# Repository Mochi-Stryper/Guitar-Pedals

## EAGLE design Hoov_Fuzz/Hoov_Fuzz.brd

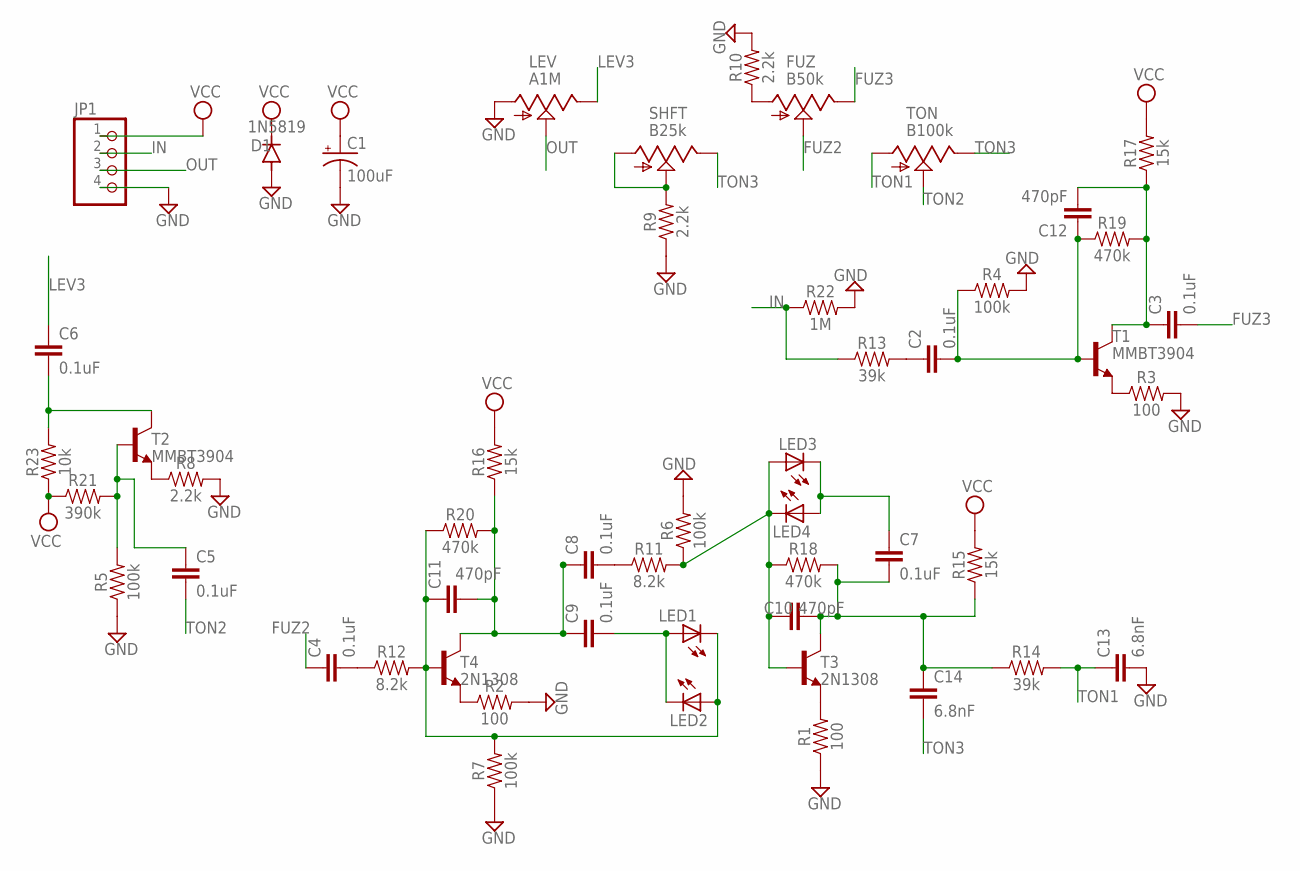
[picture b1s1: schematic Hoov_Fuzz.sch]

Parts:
C1: 100uF; PAN_B_SMD+THRU
C2, C3, C4, C5, C6, C7, C8, C9: 0.1uF; 0603
C10, C11, C12: 470pF; 0603
C13, C14: 6.8nF; 0603
D1: 1N5819; SOD123
FUZ: B50k; 9MM_SNAP-IN_POT
JP1: PINHD-1X4; 1X04
LED1, LED2, LED3, LED4: LED_E; LED_1206
LEV: A1M; 9MM_SNAP-IN_POT
R1, R2, R3: 100; 0603
R4, R5, R6, R7: 100k; 0603
R8, R9, R10: 2.2k; 0603
R11, R12: 8.2k; 0603
R13, R14: 39k; 0603
R15, R16, R17: 15k; 0603
R18, R19, R20: 470k; 0603
R21: 390k; 0603
R22: 1M; 0603
R23: 10k; 0603
SHFT: B25k; 9MM_SNAP-IN_POT
T1, T2: MMBT3904; SOT23-BEC
T3, T4: 2N1308; TO5
TON: B100k; 9MM_SNAP-IN_POT

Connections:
FUZ2: C4.1, FUZ.2 (S)
FUZ3: C3.2, FUZ.3 (E)
GND: C1.-, C1.-- (-), C13.2, D1.A, JP1.4, LEV.1 (A), R1.1, R2.2, R3.2, R4.2, R5.1, R6.2, R7.1, R8.2, R9.1, R10.2, R22.2
IN: JP1.2, R13.1, R22.1
LEV3: C6.1, LEV.3 (E)
unnamed: R9.2, SHFT.1 (A), SHFT.2 (S)
unnamed: C2.1, R13.2
unnamed: C2.2, C12.1, R4.1, R19.1, T1.B
unnamed: FUZ.1 (A), R10.1
unnamed: C3.1, C12.2, R17.1, R19.2, T1.C
unnamed: R3.1, T1.E
unnamed: C4.2, R12.1
unnamed: R2.1, T4.1 (E)
unnamed: C9.2, LED1.A, LED2.C
unnamed: C8.1, C9.1, C11.2, R16.1, R20.2, T4.3 (C)
unnamed: C11.1, LED1.C, LED2.A, R7.2, R12.2, R20.1, T4.2 (B)
unnamed: C8.2, R11.1
unnamed: C10.1, LED3.A, LED4.C, R6.1, R11.2, R18.1, T3.2 (B)
unnamed: C7.2, C10.2, C14.1, R14.1, R15.1, R18.2, T3.3 (C)
unnamed: R1.2, T3.1 (E)
unnamed: C7.1, LED3.C, LED4.A
unnamed: C5.1, R5.2, R21.2, T2.B
unnamed: C6.2, R23.2, T2.C
unnamed: R8.1, T2.E
OUT: JP1.3, LEV.2 (S)
TON1: C13.1, R14.2, TON.1 (A)
TON2: C5.2, TON.2 (S)
TON3: C14.2, SHFT.3 (E), TON.3 (E)
VCC: C1.+, C1.++ (+), D1.C, JP1.1, R15.2, R16.2, R17.2, R21.1, R23.1

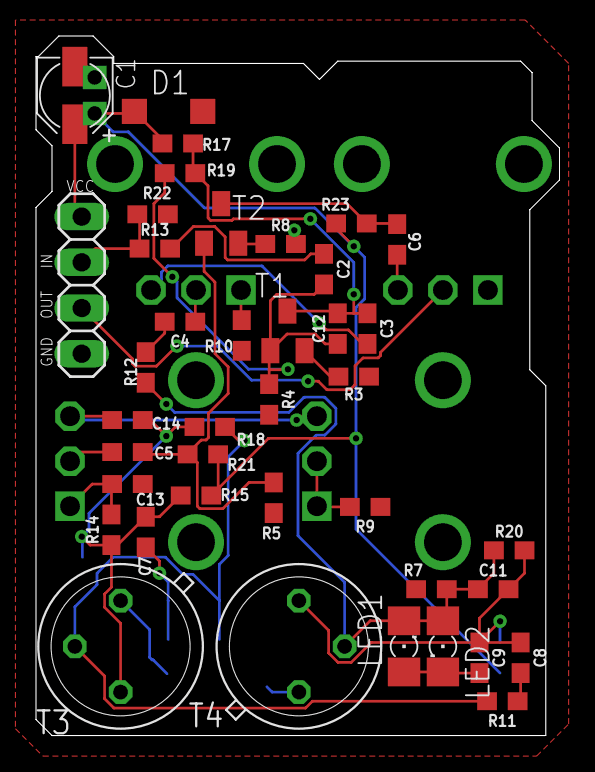
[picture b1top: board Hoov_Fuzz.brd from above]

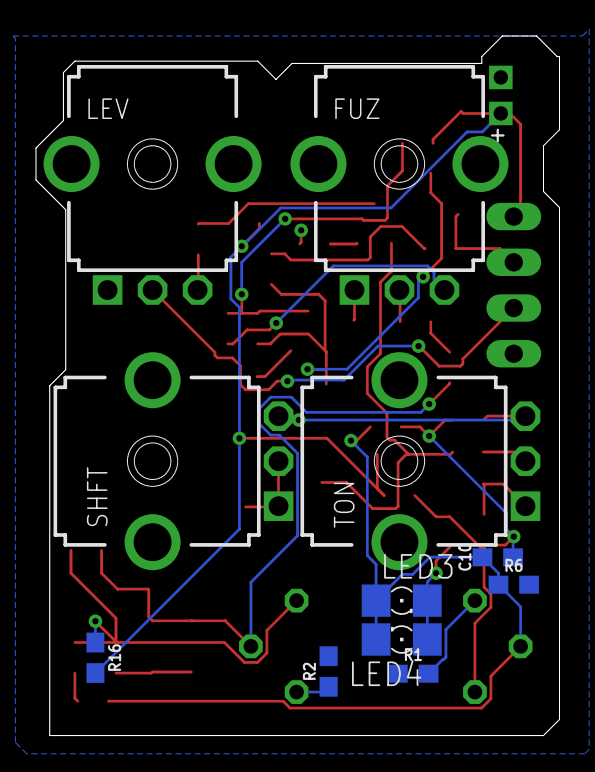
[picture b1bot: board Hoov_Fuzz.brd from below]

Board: 2 copper layers, 29.1 x 38.9 mm, 51 parts (11 on the bottom side), 29 nets.

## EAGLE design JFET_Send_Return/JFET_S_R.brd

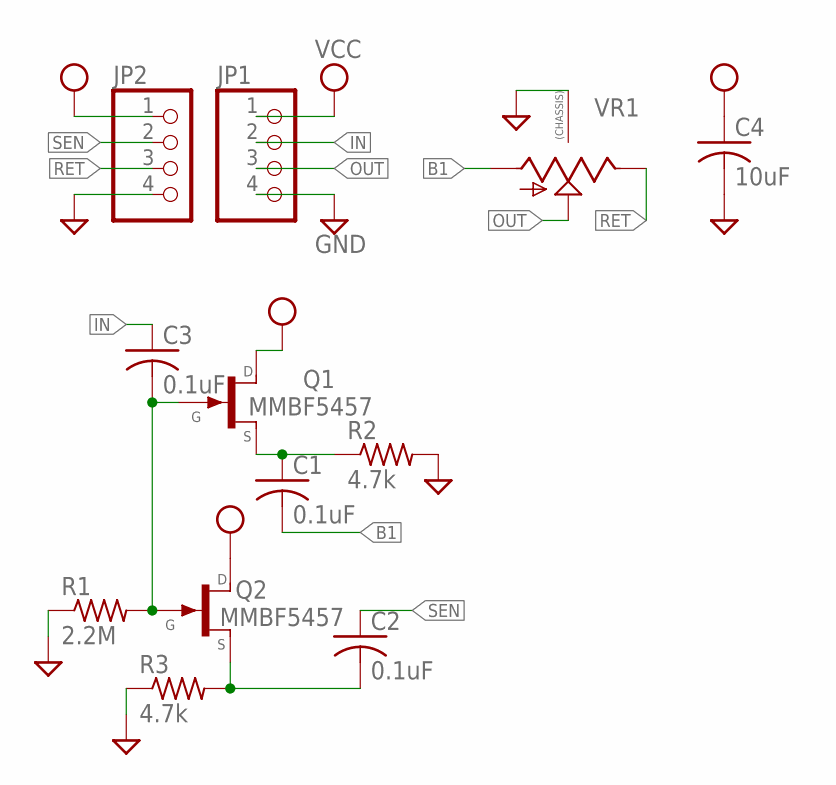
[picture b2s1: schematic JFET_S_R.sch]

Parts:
C1, C2, C3: 0.1uF; C0402
C4: 10uF; C0805
JP1, JP2: PINHD-1X4; 1X04
Q1, Q2: MMBF5457; SOT23
R1: 2.2M; R0402
R2, R3: 4.7k; R0402
VR1: 9MM_SNAP-IN_POT_CHASSIS; 9MM_SNAP-IN_POT

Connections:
B1: C1.2, VR1.1 (A)
GND: C4.2, JP1.4, JP2.4, R1.1, R2.2, R3.1, VR1.CHASSIS1, VR1.CHASSIS2
IN: C3.1, JP1.2
unnamed: C1.1, Q1.2 (S), R2.1
unnamed: C3.2, Q1.3 (G), Q2.3 (G), R1.2
unnamed: C2.2, Q2.2 (S), R3.2
OUT: JP1.3, VR1.2 (S)
RET: JP2.3, VR1.3 (E)
SEN: C2.1, JP2.2
VCC: C4.1, JP1.1, JP2.1, Q1.1 (D), Q2.1 (D)

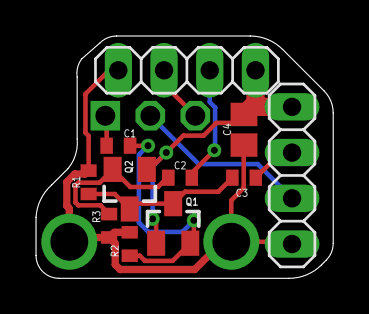
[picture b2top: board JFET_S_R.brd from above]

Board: 2 copper layers, 16.5 x 13.5 mm, 12 parts (1 on the bottom side), 10 nets.

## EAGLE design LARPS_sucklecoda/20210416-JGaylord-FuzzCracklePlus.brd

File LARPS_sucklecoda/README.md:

A Fuzz drives a Dist+ style overdrive with a swap for the LM709 for a bit of character.

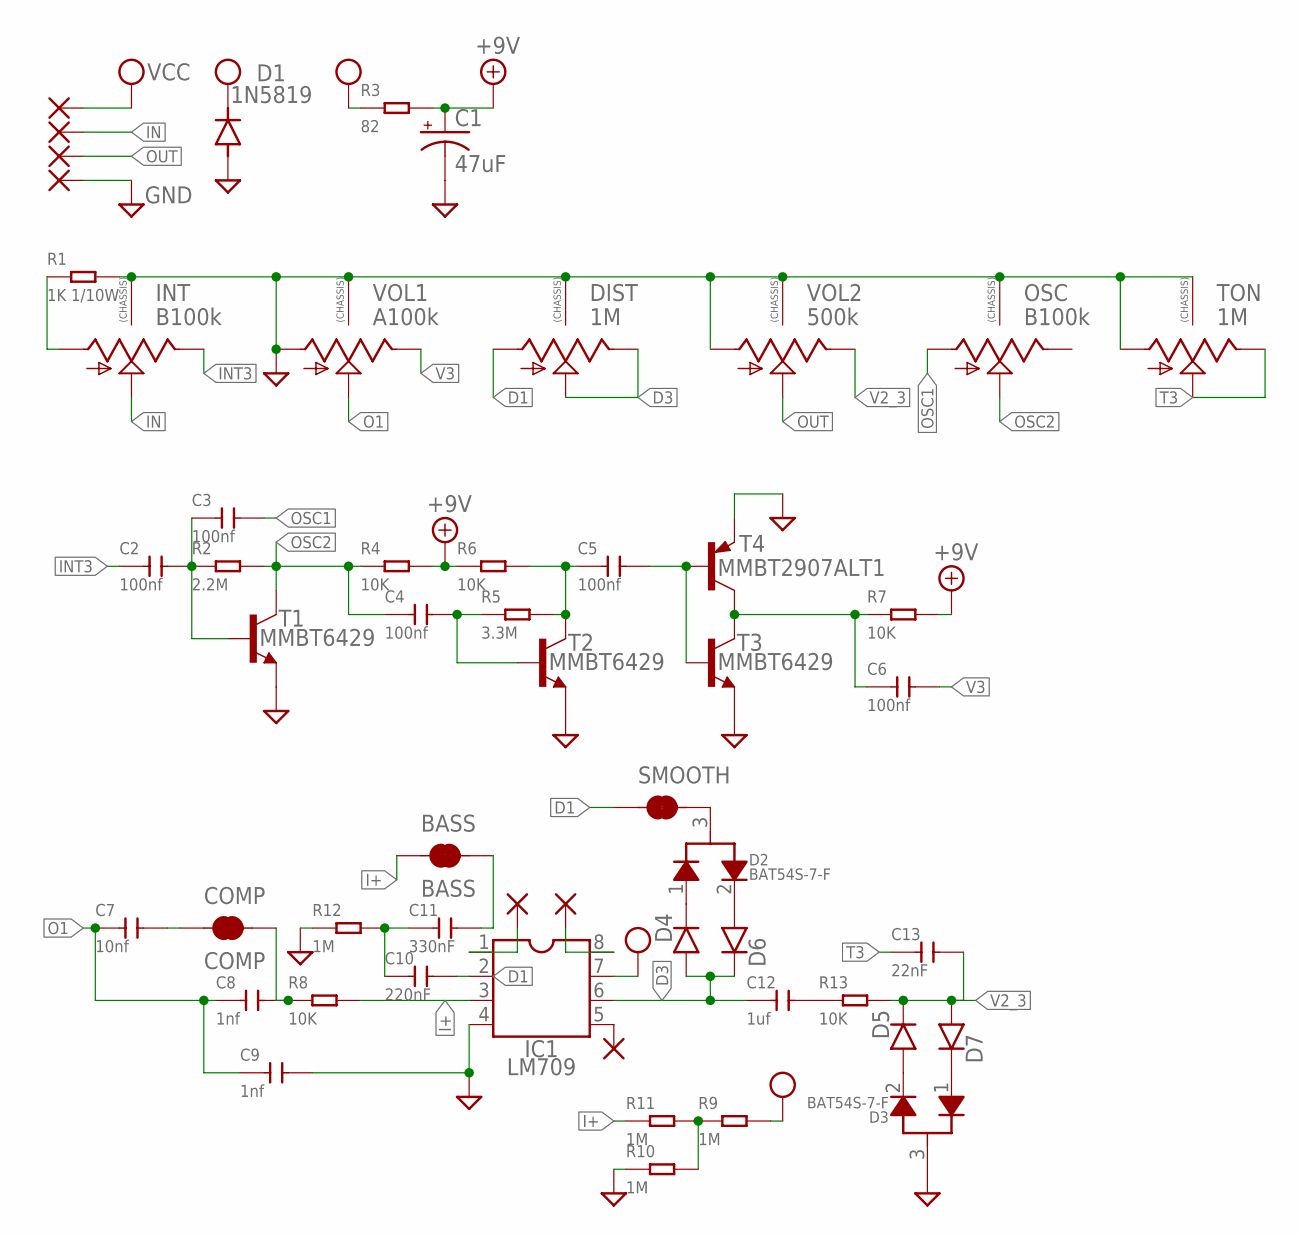
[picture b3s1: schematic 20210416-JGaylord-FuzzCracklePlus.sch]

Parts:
BASS: BASS; SMT-JUMPER_2_NC_TRACE_SILK
C1: 47uF; CPOL-RADIAL-2.5MM-6.5MM
C2, C3, C4, C5, C6: 100nf; C0603
C7: 10nf; C0603
C8, C9: 1nf; C0603
C10: 220nF; C0603
C11: 330nF; C0603
C12: 1uf; C0805
C13: 22nF; C0603
COMP: COMP; SMT-JUMPER_2_NC_TRACE_SILK
D1: 1N5819; SOD123
D2, D3: BAT54S-7-F; SOT23-3
D4, D5, D6, D7: DO35.1; DO41-1
DIST: 1M; 9MM_SNAP-IN_POT
IC1: LM709; DIP08
INT: B100k; 9MM_SNAP-IN_POT
NC, NC1, NC2: 1,6/0,8
OSC: B100k; 9MM_SNAP-IN_POT
PAD1, PAD2, PAD3, PAD4: 1,6/0,8
R1: 1K 1/10W; R0603
R2: 2.2M; R0603
R3: 82; R0603
R4, R6, R7, R8, R13: 10K; R0603
R5: 3.3M; R0603
R9, R10, R11, R12: 1M; R0603
SMOOTH: JUMPER-SMT_2_NC_TRACE_SILK; SMT-JUMPER_2_NC_TRACE_SILK
T1, T2, T3: MMBT6429; SOT23-BEC
T4: MMBT2907ALT1; SOT23-BEC
TON: 1M; 9MM_SNAP-IN_POT
VOL1: A100k; 9MM_SNAP-IN_POT
VOL2: 500k; 9MM_SNAP-IN_POT

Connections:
+9V: C1.1 (+), R3.2, R4.2, R6.1, R7.2
D1: C10.2, DIST.1 (A), IC1.2, SMOOTH.1
D3: C12.1, D4.A, D6.C, DIST.2 (S), DIST.3 (E), IC1.6
GND: C1.2 (-), C9.2, D1.A, D3.3, DIST.CHASSIS1, DIST.CHASSIS2, IC1.4, INT.CHASSIS1, INT.CHASSIS2, OSC.CHASSIS1, OSC.CHASSIS2, PAD4.1, R1.2, R10.1, R12.1, T1.E, T2.E, T3.E, T4.E, TON.1 (A), TON.CHASSIS1, TON.CHASSIS2, VOL1.1 (A), VOL1.CHASSIS1, VOL1.CHASSIS2, VOL2.1 (A), VOL2.CHASSIS1, VOL2.CHASSIS2
I+: BASS.1, IC1.3, R8.2, R11.1
IN: INT.2 (S), PAD2.1
INT3: C2.1, INT.3 (E)
unnamed: C2.2, C3.1, R2.1, T1.B
unnamed: INT.1 (A), R1.1
unnamed: C4.2, R5.1, T2.B
unnamed: C5.1, R5.2, R6.2, T2.C
unnamed: C6.1, R7.1, T3.C, T4.C
unnamed: C5.2, T3.B, T4.B
unnamed: C8.2, COMP.2, R8.1
unnamed: R9.1, R10.2, R11.2
unnamed: IC1.1, NC.1
unnamed: D2.1, D4.C
unnamed: C7.2, COMP.1
unnamed: D2.2, D6.A
unnamed: BASS.2, C11.2
unnamed: IC1.8, NC1.1
unnamed: C12.2, R13.1
unnamed: IC1.5, NC2.1
unnamed: D3.2, D5.A
unnamed: C10.1, C11.1, R12.2
unnamed: D3.1, D7.C
unnamed: D2.3, SMOOTH.2
O1: C7.1, C8.1, C9.1, VOL1.2 (S)
OSC1: C3.2, OSC.1 (A)
OSC2: C4.1, OSC.2 (S), R2.2, R4.1, T1.C
OUT: PAD3.1, VOL2.2 (S)
T3: C13.1, TON.2 (S), TON.3 (E)
V2_3: C13.2, D5.C, D7.A, R13.2, VOL2.3 (E)
V3: C6.2, VOL1.3 (E)
VCC: D1.C, IC1.7, PAD1.1, R3.1, R9.2

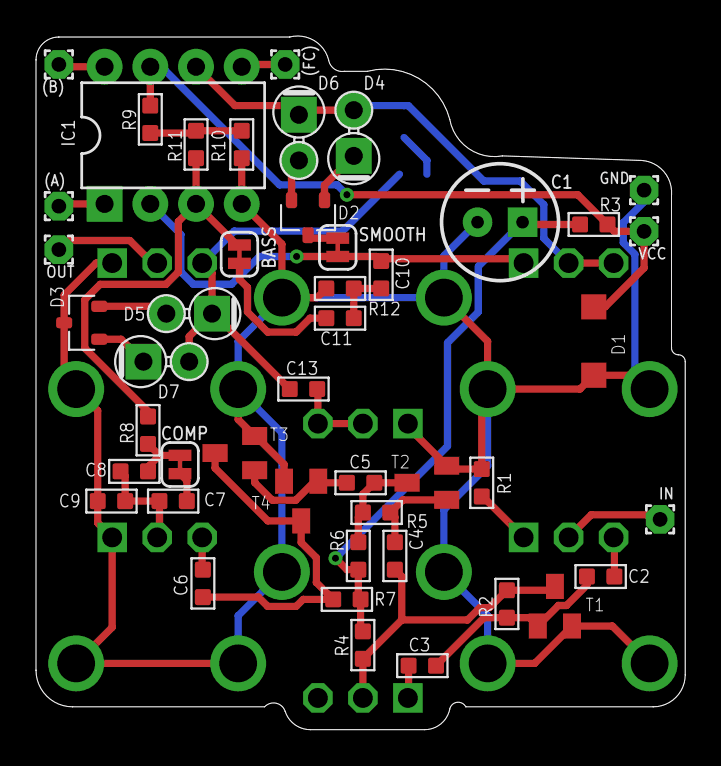
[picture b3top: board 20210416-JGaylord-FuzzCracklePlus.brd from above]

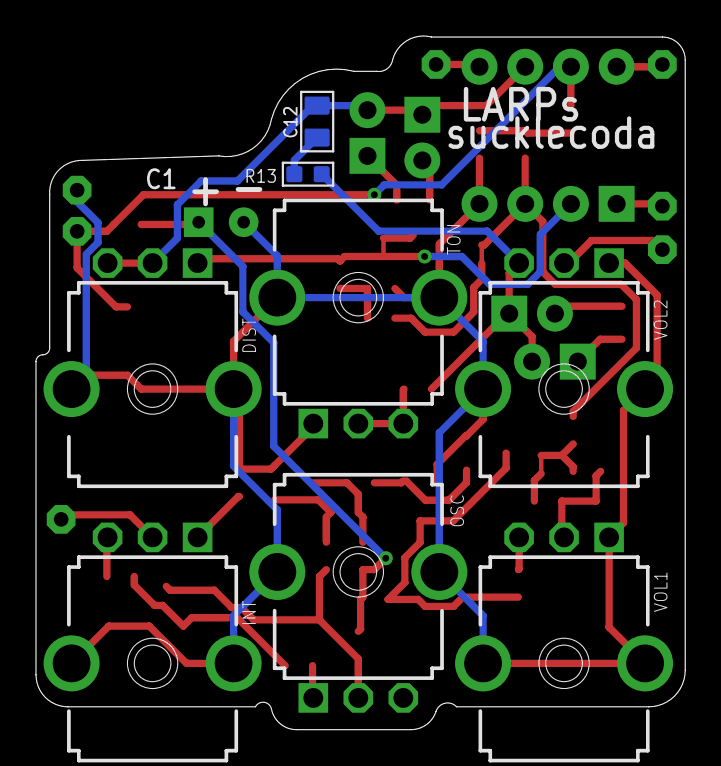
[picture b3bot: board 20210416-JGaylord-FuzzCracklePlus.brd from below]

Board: 2 copper layers, 36.1 x 38.5 mm, 54 parts (8 on the bottom side), 35 nets.

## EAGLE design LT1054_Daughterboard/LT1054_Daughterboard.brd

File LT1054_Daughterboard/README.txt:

+9V to +/-12V converter
Inspiration: Campus THAT Jam v1.4 Power Supply/Mutable Instruments Breadboard Friends
LT1054 generates voltages that are trimmed and regulated by 12V zener diodes.
Precariously mates to Lumberg 1614-09 jack.
SMT pads for +12V, -12V, and 0V rails.
Design considerations:
-The LT1054 is not a viable solution for supplying more than 100 mA on the negative rail.
-It is difficult to trim voltages on the top side of the board while measuring the voltages exposed via the pads on the bottom side of the board.
-The 100uF capacitors must be placed with care. They may be bent to the side to maintain a thinner profile, and reduce the chances of shorting with nearby components.

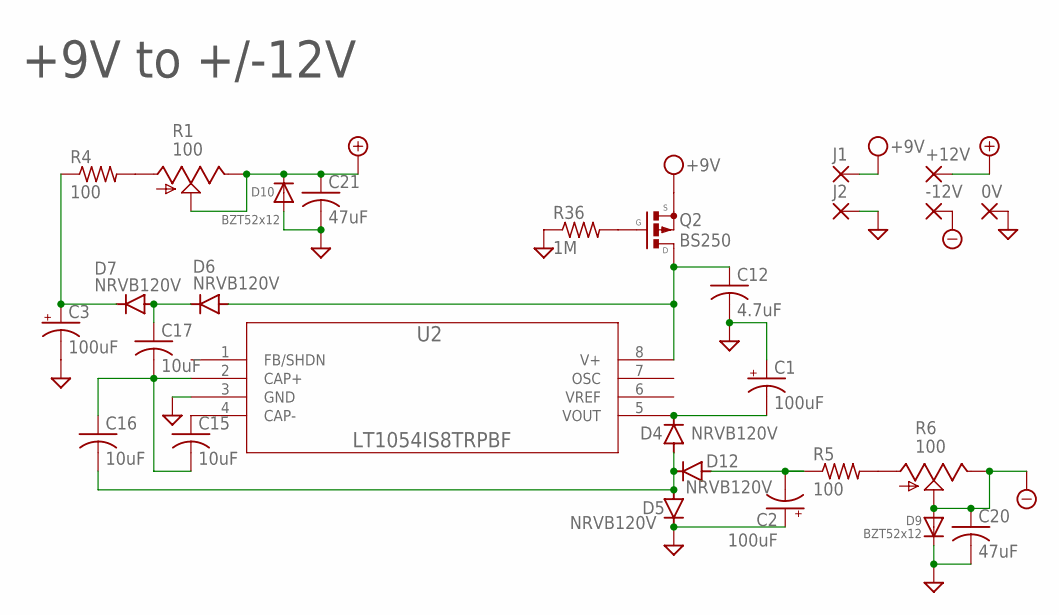
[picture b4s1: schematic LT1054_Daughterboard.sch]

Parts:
0V: SMD2; SMD1,27-2,54
+12V: SMD2; SMD1,27-2,54
-12V: SMD2; SMD1,27-2,54
C1, C2, C3: 100uF; E2,5-6E
C12: 4.7uF; C0805
C15, C16, C17: 10uF; C1206
C20, C21: 47uF; C1206
D4, D5, D6, D7, D12: NRVB120V; SOD123
D9, D10: BZT52x12; SOD-123
J1: SMD2; SMD1,27-2,54
J2: 1,6/0,8
Q2: BS250; SOT23
R1, R6: 100; 3223G
R4, R5: 100; R1206
R36: 1M; R0805
U2: LT1054IS8TRPBF; SO-8_S

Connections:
+12V: +12V.1, C21.1, D10.C, R1.2 (S), R1.3 (E)
-12V: -12V.1, C20.1, D9.A, R6.2 (S), R6.3 (E)
GND: 0V.1, C1.+, C2.+, C3.-, C12.2, C20.2, C21.2, D5.C, D9.C, D10.A, J2.1, R36.1, U2.3 (GND)
unnamed: R1.1 (A), R4.2
unnamed: R5.2, R6.1 (A)
unnamed: Q2.G, R36.2
unnamed: C12.1, D6.A, Q2.D, U2.8 (V+)
unnamed: C1.-, D4.C, U2.5 (VOUT)
unnamed: C16.2, D4.A, D5.A, D12.C
unnamed: C2.-, D12.A, R5.1
unnamed: C15.1, U2.4 (CAP-)
unnamed: C15.2, C16.1, C17.2, U2.2 (CAP+)
unnamed: C17.1, D6.C, D7.A
unnamed: C3.+, D7.C, R4.1
VCC: J1.1, Q2.S
VREF: U2.6 (VREF)

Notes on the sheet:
+9V to +/-12V

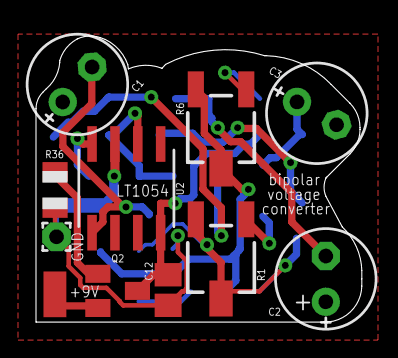
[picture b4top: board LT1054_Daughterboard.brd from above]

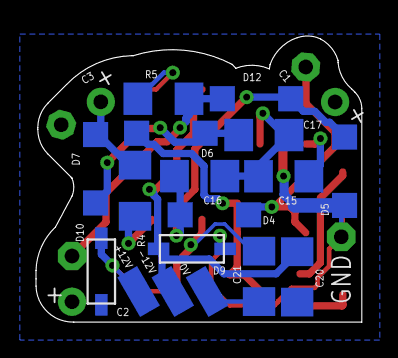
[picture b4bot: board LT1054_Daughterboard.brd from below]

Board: 2 copper layers, 18.1 x 15.9 mm, 28 parts (17 on the bottom side), 15 nets.

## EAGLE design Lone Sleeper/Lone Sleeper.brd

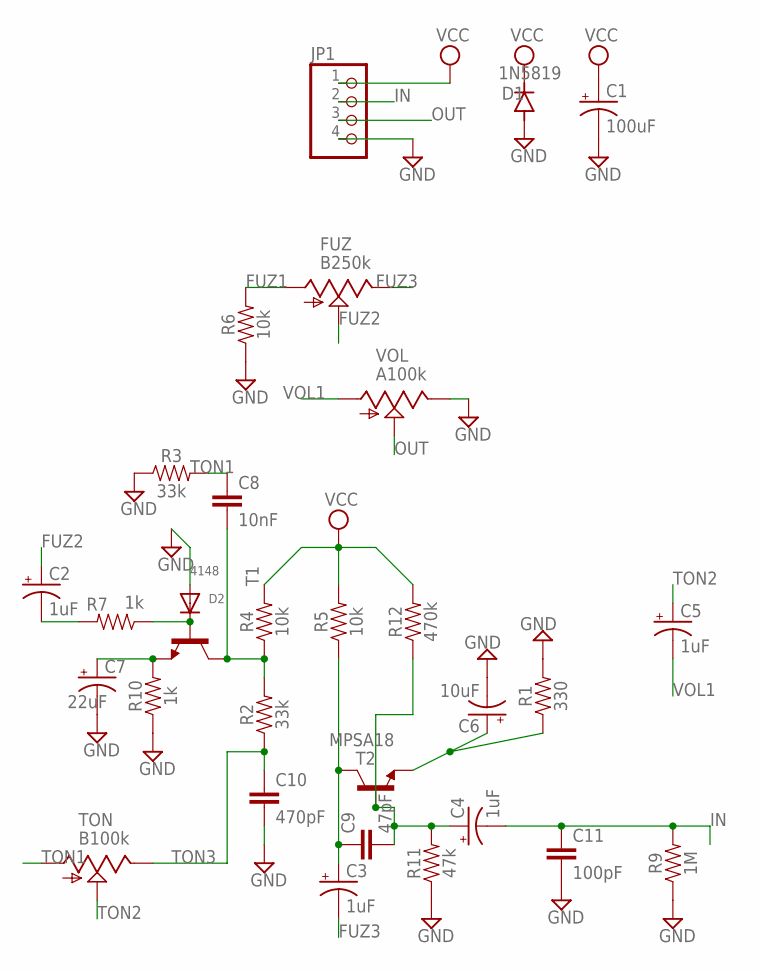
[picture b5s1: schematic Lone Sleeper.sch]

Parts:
C1: 100uF; PAN_B_SMD+THRU
C2, C3, C4, C5: 1uF; PAN_B_SMD+THRU
C6: 10uF; PAN_B_SMD+THRU
C7: 22uF; PAN_B_SMD+THRU
C8: 10nF; 0603
C9: 47pF; 0603
C10: 470pF; 0603
C11: 100pF; 0603
D1: 1N5819; SOD123
D2: 4148; SOD-123
FUZ: B250k; 9MM_SNAP-IN_POT
JP1: PINHD-1X4; 1X04
R1: 330; 0603
R2, R3: 33k; 0603
R4, R5, R6: 10k; 0603
R7, R10: 1k; 0603
R9: 1M; 0603
R11: 47k; 0603
R12: 470k; 0603
T1: -NPN-TO5; TO5
T2: MPSA18; TO92-EBC
TON: B100k; 9MM_SNAP-IN_POT
VOL: A100k; 9MM_SNAP-IN_POT

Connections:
FUZ1: FUZ.1 (A), R6.2
FUZ2: C2.+, C2.++ (+), FUZ.2 (S)
FUZ3: C3.-, C3.-- (-), FUZ.3 (E)
GND: C1.-, C1.-- (-), C6.-, C6.-- (-), C7.-, C7.-- (-), C10.2, C11.2, D1.A, D2.A, JP1.4, R1.2, R3.1, R6.1, R9.1, R10.1, R11.1, VOL.3 (E)
IN: C4.-, C4.-- (-), C11.1, JP1.2, R9.2
unnamed: C8.2, R2.2, R4.1, T1.3 (C)
unnamed: C7.+, C7.++ (+), R10.2, T1.1 (E)
unnamed: D2.C, R7.1, T1.2 (B)
unnamed: C2.-, C2.-- (-), R7.2
unnamed: C3.+, C3.++ (+), C9.1, R5.1, T2.C
unnamed: C4.+, C4.++ (+), C9.2, R11.2, R12.1, T2.B
unnamed: C6.+, C6.++ (+), R1.1, T2.E
OUT: JP1.3, VOL.2 (S)
TON1: C8.1, R3.2, TON.1 (A)
TON2: C5.+, C5.++ (+), TON.2 (S)
TON3: C10.1, R2.1, TON.3 (E)
VCC: C1.+, C1.++ (+), D1.C, JP1.1, R4.2, R5.2, R12.2
VOL1: C5.-, C5.-- (-), VOL.1 (A)

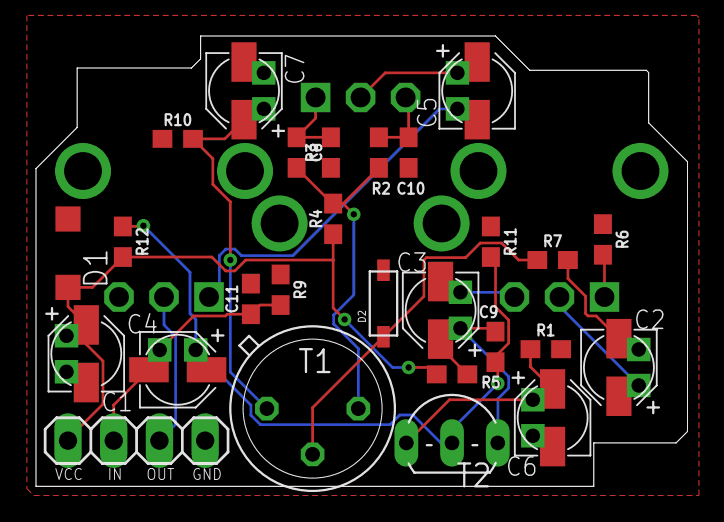
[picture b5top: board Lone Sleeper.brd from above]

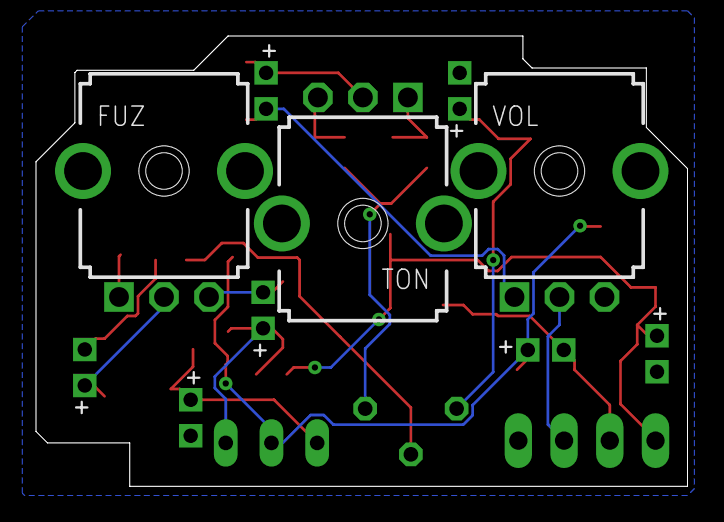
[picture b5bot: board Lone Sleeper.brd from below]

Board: 2 copper layers, 36.2 x 25.0 mm, 30 parts (3 on the bottom side), 18 nets.

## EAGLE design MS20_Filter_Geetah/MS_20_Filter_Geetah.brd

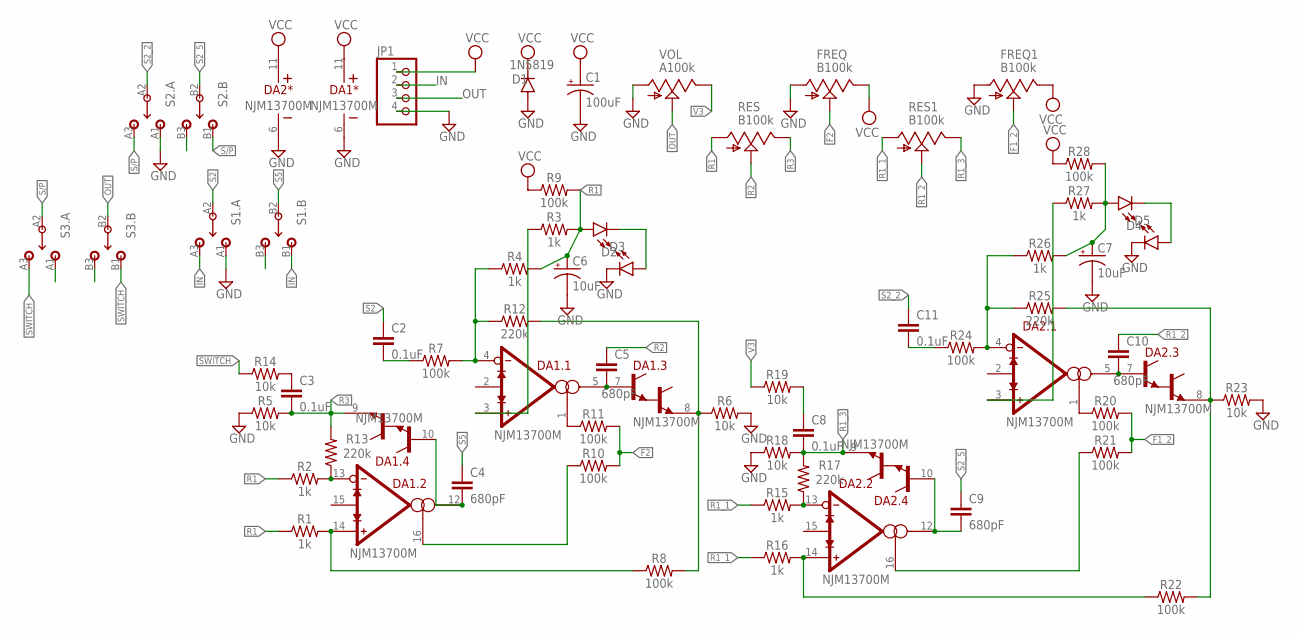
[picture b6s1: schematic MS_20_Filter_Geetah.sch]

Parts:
C1: 100uF; PAN_B_SMD+THRU
C2, C3, C8, C11: 0.1uF; 0603
C4, C5, C9, C10: 680pF; 0603
C6, C7: 10uF; PAN_B_SMD+THRU
D1: 1N5819; SOD123
D2, D3, D4, D5: LED-FKIT-1206; FKIT-LED-1206
DA1, DA2: NJM13700M; SO-16
FREQ, FREQ1: B100k; 9MM_SNAP-IN_POT
JP1: PINHD-1X4; 1X04
R1, R2, R3, R4, R15, R16, R26, R27: 1k; 0603
R5, R6, R14, R18, R19, R23: 10k; 0603
R7, R8, R9, R10, R11, R20, R21, R22, R24, R28: 100k; 0603
R12, R13, R17, R25: 220k; 0603
RES, RES1: B100k; 9MM_SNAP-IN_POT
S1, S2, S3: DPDT.LUGS
VOL: A100k; 9MM_SNAP-IN_POT

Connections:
F1_2: FREQ1.2 (S), R20.2, R21.2
F2: FREQ.2 (S), R10.2, R11.2
GND: C1.-, C1.-- (-), C6.-, C6.-- (-), C7.-, C7.-- (-), D1.A, D3.C, D5.C, DA1.6 (V-), DA2.6 (V-), FREQ.1 (A), FREQ1.1 (A), JP1.4, R5.1, R6.2, R18.1, R23.2, S1.A1 (1), S2.A1 (1), VOL.1 (A)
IN: JP1.2, S1.A3 (3), S1.B1 (1)
unnamed: C2.2, R7.1
unnamed: DA1.4 (IN-), R4.1, R7.2, R12.1
unnamed: DA1.1 (AMP_BIAS), R11.1
unnamed: C5.2, DA1.5 (OUT), DA1.7 (B)
unnamed: DA1.8 (E), R6.1, R8.2, R12.2
unnamed: DA1.3 (IN+), R3.1
unnamed: DA1.16 (AMP_BIAS), R10.1
unnamed: D2.C, D3.A
unnamed: C4.2, DA1.10 (B), DA1.12 (OUT)
unnamed: DA1.13 (IN-), R2.2, R13.1
unnamed: C3.1, R14.2
unnamed: DA1.14 (IN+), R1.2, R8.1
unnamed: DA2.13 (IN-), R15.2, R17.1
unnamed: DA2.14 (IN+), R16.2, R22.1
unnamed: C8.1, R19.2
unnamed: DA2.1 (AMP_BIAS), R20.1
unnamed: C9.2, DA2.10 (B), DA2.12 (OUT)
unnamed: DA2.16 (AMP_BIAS), R21.1
unnamed: C10.2, DA2.5 (OUT), DA2.7 (B)
unnamed: DA2.8 (E), R22.2, R23.1, R25.2
unnamed: DA2.4 (IN-), R24.2, R25.1, R26.1
unnamed: C11.2, R24.1
unnamed: DA2.3 (IN+), R27.1
unnamed: D4.C, D5.A
unnamed: C7.+, C7.++ (+), D4.A, R26.2, R27.2, R28.2
OUT: JP1.3, S3.B2 (2), VOL.2 (S)
R1: C6.+, C6.++ (+), D2.A, R1.1, R2.1, R3.2, R4.2, R9.2, RES.1 (A)
R1_1: R15.1, R16.1, RES1.1 (A)
R1_2: C10.1, RES1.2 (S)
R1_3: C8.2, DA2.9 (E), R17.2, R18.2, RES1.3 (E)
R2: C5.1, RES.2 (S)
R3: C3.2, DA1.9 (E), R5.2, R13.2, RES.3 (E)
S2: C2.1, S1.A2 (2)
S2_2: C11.1, S2.A2 (2)
S2_5: C9.1, S2.B2 (2)
S5: C4.1, S1.B2 (2)
S/P: S2.A3 (3), S2.B1 (1), S3.A2 (2)
SWITCH: R14.1, S3.A3 (3), S3.B1 (1)
V3: R19.1, VOL.3 (E)
VCC: C1.+, C1.++ (+), D1.C, DA1.11 (V+), DA2.11 (V+), FREQ.3 (E), FREQ1.3 (E), JP1.1, R9.1, R28.1

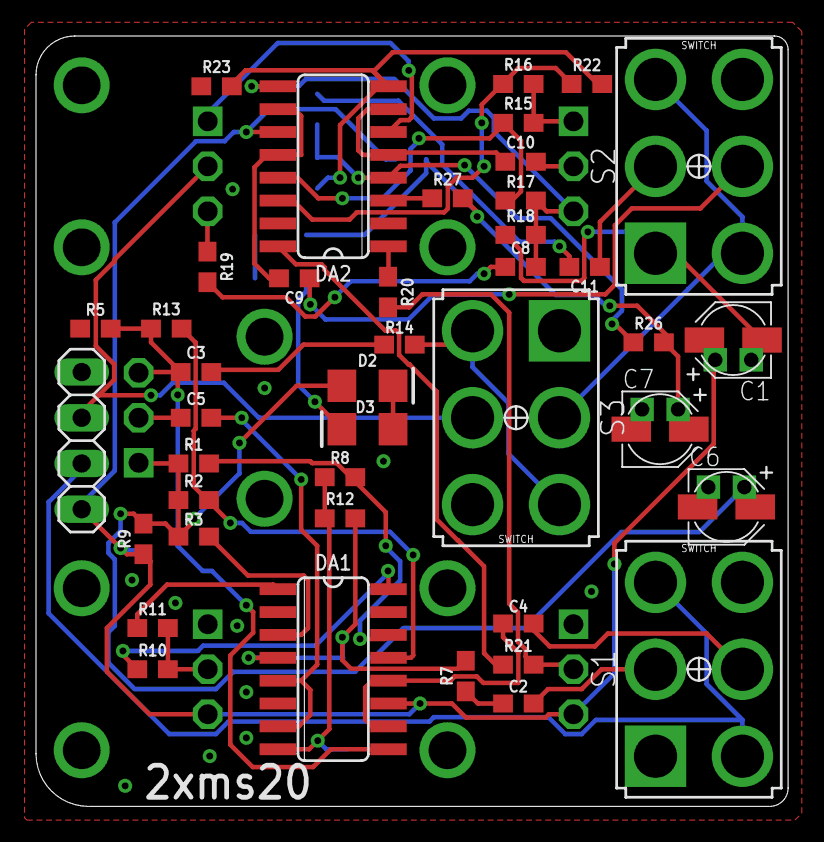
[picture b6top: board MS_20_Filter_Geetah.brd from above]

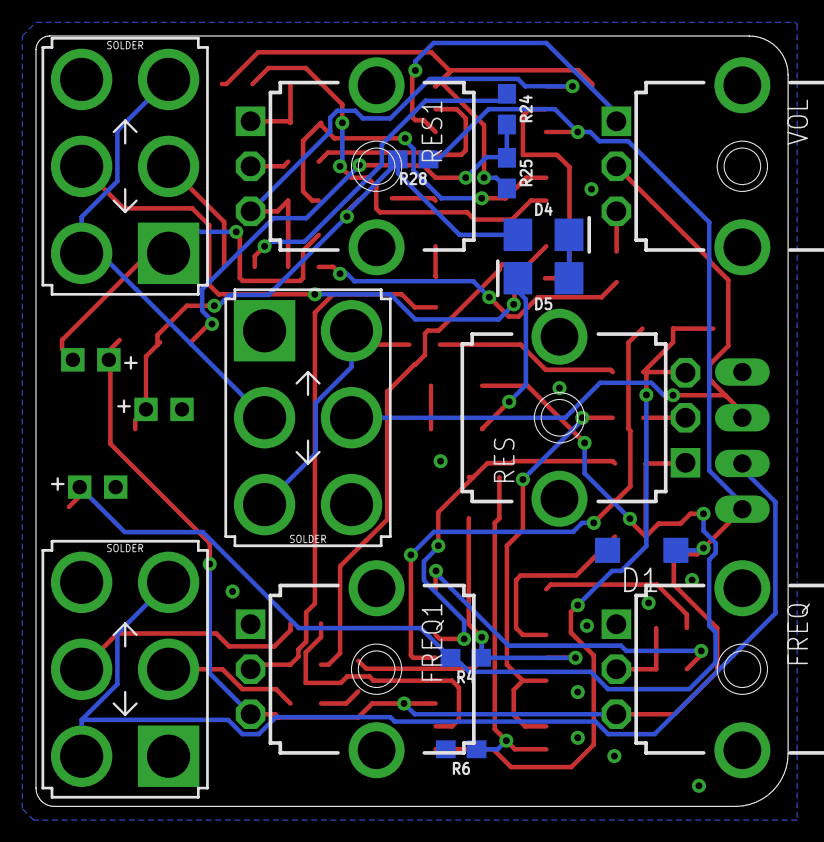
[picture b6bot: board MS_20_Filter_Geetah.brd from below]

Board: 2 copper layers, 41.8 x 42.8 mm, 55 parts (16 on the bottom side), 44 nets.

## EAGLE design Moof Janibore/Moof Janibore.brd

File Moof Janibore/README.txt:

Mojo Hand FX
Iron Bell
Modded Tubescreamer
Substitutions:
BC550 subbed for BC850
2N5088 subbed for MMBT5088

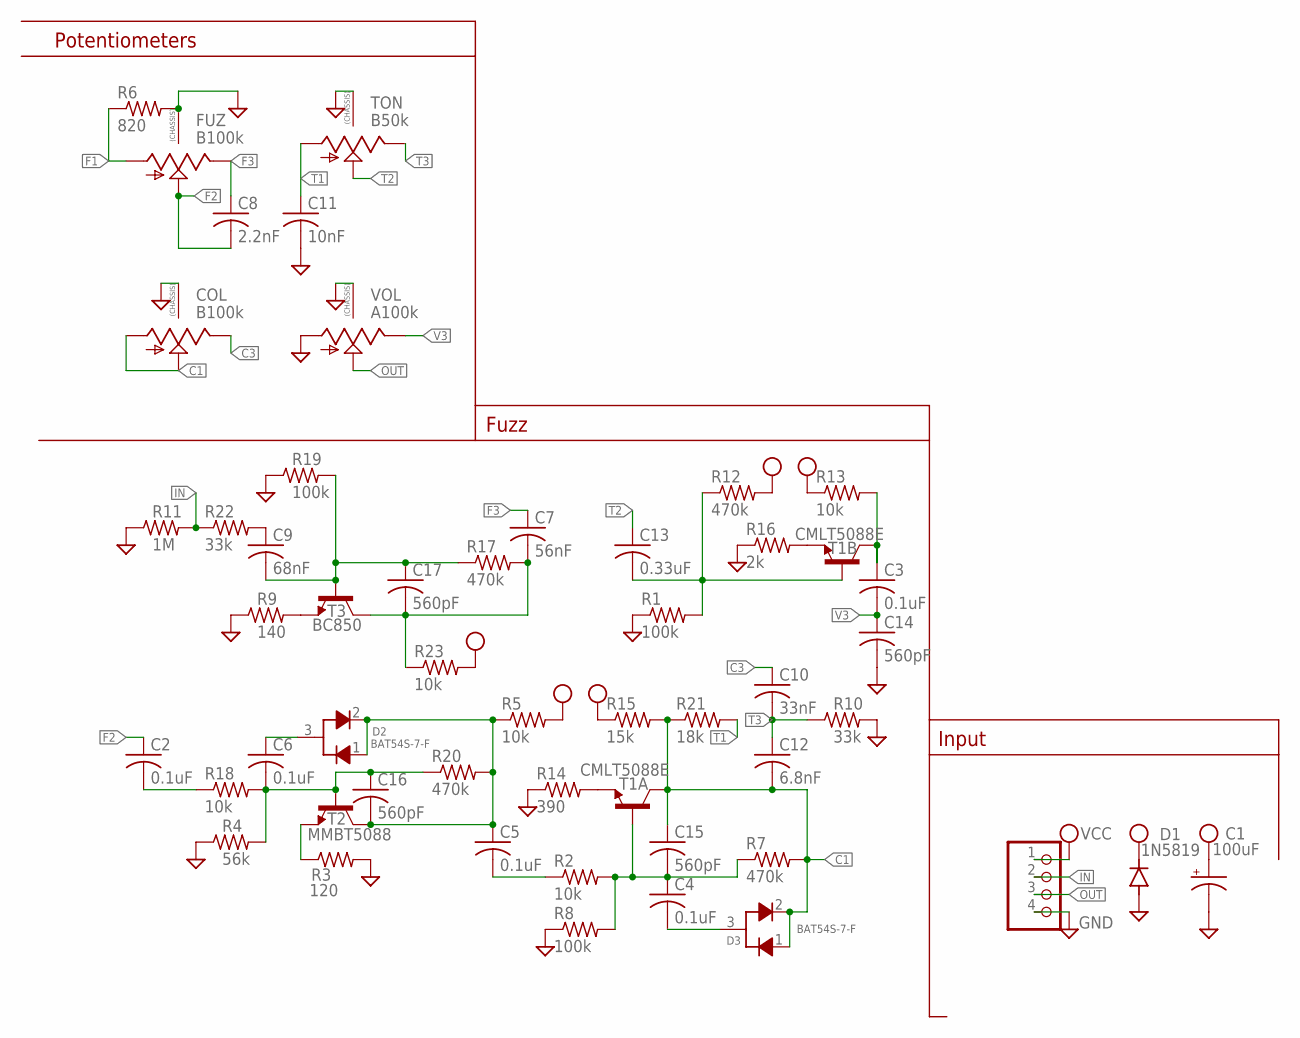
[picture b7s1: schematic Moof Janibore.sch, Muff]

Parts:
C1: 100uF; PAN_B_SMD+THRU
C2, C3, C4, C5, C6: 0.1uF; C0402
C7: 56nF; C0402
C8: 2.2nF; C0402
C9: 68nF; C0402
C10: 33nF; C0402
C11: 10nF; C0402
C12: 6.8nF; C0402
C13: 0.33uF; C0402
C14, C15, C16, C17: 560pF; C0402
COL: B100k; 9MM_SNAP-IN_POT
D1: 1N5819; SOD123
D2, D3: BAT54S-7-F; SOT23-3
FUZ: B100k; 9MM_SNAP-IN_POT
JP1: PINHD-1X4; 1X04
R1, R8, R19: 100k; R0402
R2, R5, R13, R18, R23: 10k; R0402
R3: 120; R0402
R4: 56k; R0402
R6: 820; R0402
R7, R12, R17, R20: 470k; R0402
R9: 140; R0402
R10, R22: 33k; R0402
R11: 1M; R0402
R14: 390; R0402
R15: 15k; R0402
R16: 2k; R0402
R21: 18k; R0402
T1: CMLT5088E; SOT563
T2: MMBT5088; SOT23-BEC
T3: BC850; SOT23-BEC
TON: B50k; 9MM_SNAP-IN_POT
VOL: A100k; 9MM_SNAP-IN_POT

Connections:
C1: C12.2, C15.1, COL.1 (A), COL.2 (S), D3.1, D3.2, R7.2, R15.2, R21.1, T1.6 (C)
C3: C10.1, COL.3 (E)
F1: FUZ.1 (A), R6.1
F2: C2.1, C8.2, FUZ.2 (S)
F3: C7.1, C8.1, FUZ.3 (E)
GND: C1.-, C1.-- (-), C11.2, C14.2, COL.CHASSIS1, COL.CHASSIS2, D1.A, FUZ.CHASSIS1, FUZ.CHASSIS2, JP1.4, R1.1, R3.2, R4.1, R6.2, R8.1, R9.1, R10.2, R11.1, R14.1, R16.1, R19.1, TON.CHASSIS1, TON.CHASSIS2, VOL.1 (A), VOL.CHASSIS1, VOL.CHASSIS2
IN: JP1.2, R11.2, R22.1
unnamed: C9.1, R22.2
unnamed: C7.2, C17.2, R17.2, R23.1, T3.C
unnamed: C9.2, C17.1, R17.1, R19.2, T3.B
unnamed: R9.2, T3.E
unnamed: C2.2, R18.1
unnamed: C6.2, C16.1, R4.2, R18.2, R20.1, T2.B
unnamed: R3.1, T2.E
unnamed: C5.2, R2.1
unnamed: C6.1, D2.3
unnamed: C5.1, C16.2, D2.1, D2.2, R5.1, R20.2, T2.C
unnamed: C4.1, C15.2, R2.2, R7.1, R8.2, T1.2 (B)
unnamed: R14.2, T1.1 (E)
unnamed: R16.2, T1.4 (E)
unnamed: C13.2, R1.2, R12.1, T1.5 (B)
unnamed: C4.2, D3.3
unnamed: C3.1, R13.2, T1.3 (C)
OUT: JP1.3, VOL.2 (S)
T1: C11.1, R21.2, TON.1 (A)
T2: C13.1, TON.2 (S)
T3: C10.2, C12.1, R10.1, TON.3 (E)
V3: C3.2, C14.1, VOL.3 (E)
VCC: C1.+, C1.++ (+), D1.C, JP1.1, R5.2, R12.2, R13.1, R15.1, R23.2

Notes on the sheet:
Potentiometers
Fuzz
Input

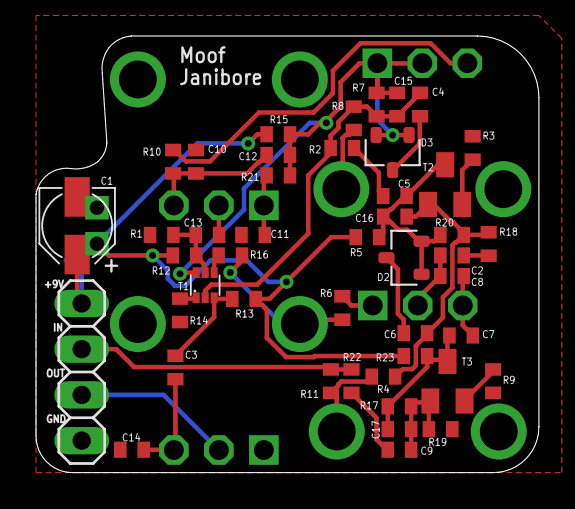
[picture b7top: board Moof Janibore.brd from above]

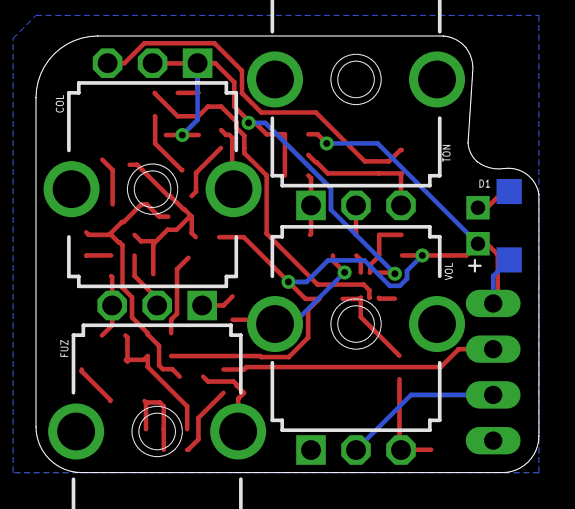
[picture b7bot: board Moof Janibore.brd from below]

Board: 2 copper layers, 27.9 x 24.3 mm, 51 parts (5 on the bottom side), 29 nets.

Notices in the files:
parts and their libraries:
SparkFun-Capacitors: Licensing: Creative Commons ShareAlike 4.0 International - https://creativecommons.org/licenses/by-sa/4.0
